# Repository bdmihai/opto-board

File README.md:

# opto-board

A small isolated interface board that lets a microcontroller set and read analog voltages and exchange digital ON/OFF signals with a separate high-voltage domain. Nothing connects the two sides except the optocouplers, so ground loops and interference stay out of the low-voltage electronics. The board is designed in KiCad and was built as a test fixture.

## Schematic

The board has two kinds of channels across the isolation barrier.

**Digital (4 × PC817).** These carry ON/OFF signals, such as an active-low fault input. On the HV side, a 4.7 kΩ pull-up to +15 V drives the LED with about 2.9 mA. On the LV side, the phototransistor pulls a 10 kΩ pull-up to 3.3 V low, and a 10 nF capacitor filters short spikes. That only needs a CTR of about 19 %, well under the 50 % the PC817 guarantees. In the MCU → HV direction, the MCU pin sources the LED current, so an unpowered MCU leaves the output in a safe state.

**Analog (2 × HCNR201).** These carry 0–3.3 V on the MCU side and 0–10 V on the HV side, in both directions: one channel sets a voltage and one measures it. Each HCNR201 has one LED and two matched photodiodes. An op-amp servo loop drives the LED so that the input photodiode current equals V_IN / R_IN. This cancels out LED drift from temperature, part spread and aging. On the other side, a transimpedance amplifier turns the output photodiode current back into a voltage:

V_OUT / V_IN = K3 · R_OUT / R_IN

K3 differs from part to part, so R_OUT includes a trimmer and each channel is calibrated once. The full-scale photodiode current of about 25 µA sits in the linear range of the HCNR201, where the datasheet specifies 0.05 % nonlinearity.

The LV side runs from 12 V through a fuse, a TVS diode and a buck converter that makes 3.3 V. The HV side is powered from the +15 V auxiliary output of the device being controlled. A 10 MΩ bleed (2 × 20 MΩ) connects HV_GND to GND so the HV ground cannot float to an arbitrary voltage.

## Board layout

| | |
|---|---|
| Size | 65 × 75 mm, 1.6 mm FR-4, 4 layers |
| Isolation slot | 55 × 5 mm, milled through the board |
| Copper-free gap | 9 mm between domains on every layer, including the inner planes |
| Narrowest point | PC817 package, 7.62 mm between the pad rows |
| Indicators | PWR, FAULT, OVT and EOCH LEDs on the LV side |

No copper from one domain runs under the other one on any layer. The slot forces surface creepage to go around it instead of straight across. This is a test board: the spacing is a design target, not a certified isolation rating.

## PCB production

[PCBWay](https://www.pcbway.com/) manufactured the PCBs as part of a sponsorship. 

The isolation slot was milled cleanly, there were no solder mask, copper or via defects, and the matte solder mask made hand soldering easy. The board worked on the first try and did the job!

## Results

In a loopback test (setpoint output wired to the measurement input, 2360 readings), the gain error was −0.13 % and 94 % of readings fell within one 8-bit step of the setpoint. Each channel behaves like a low-pass filter of about 1 kHz, and the full loopback settles in about 1.5 ms.

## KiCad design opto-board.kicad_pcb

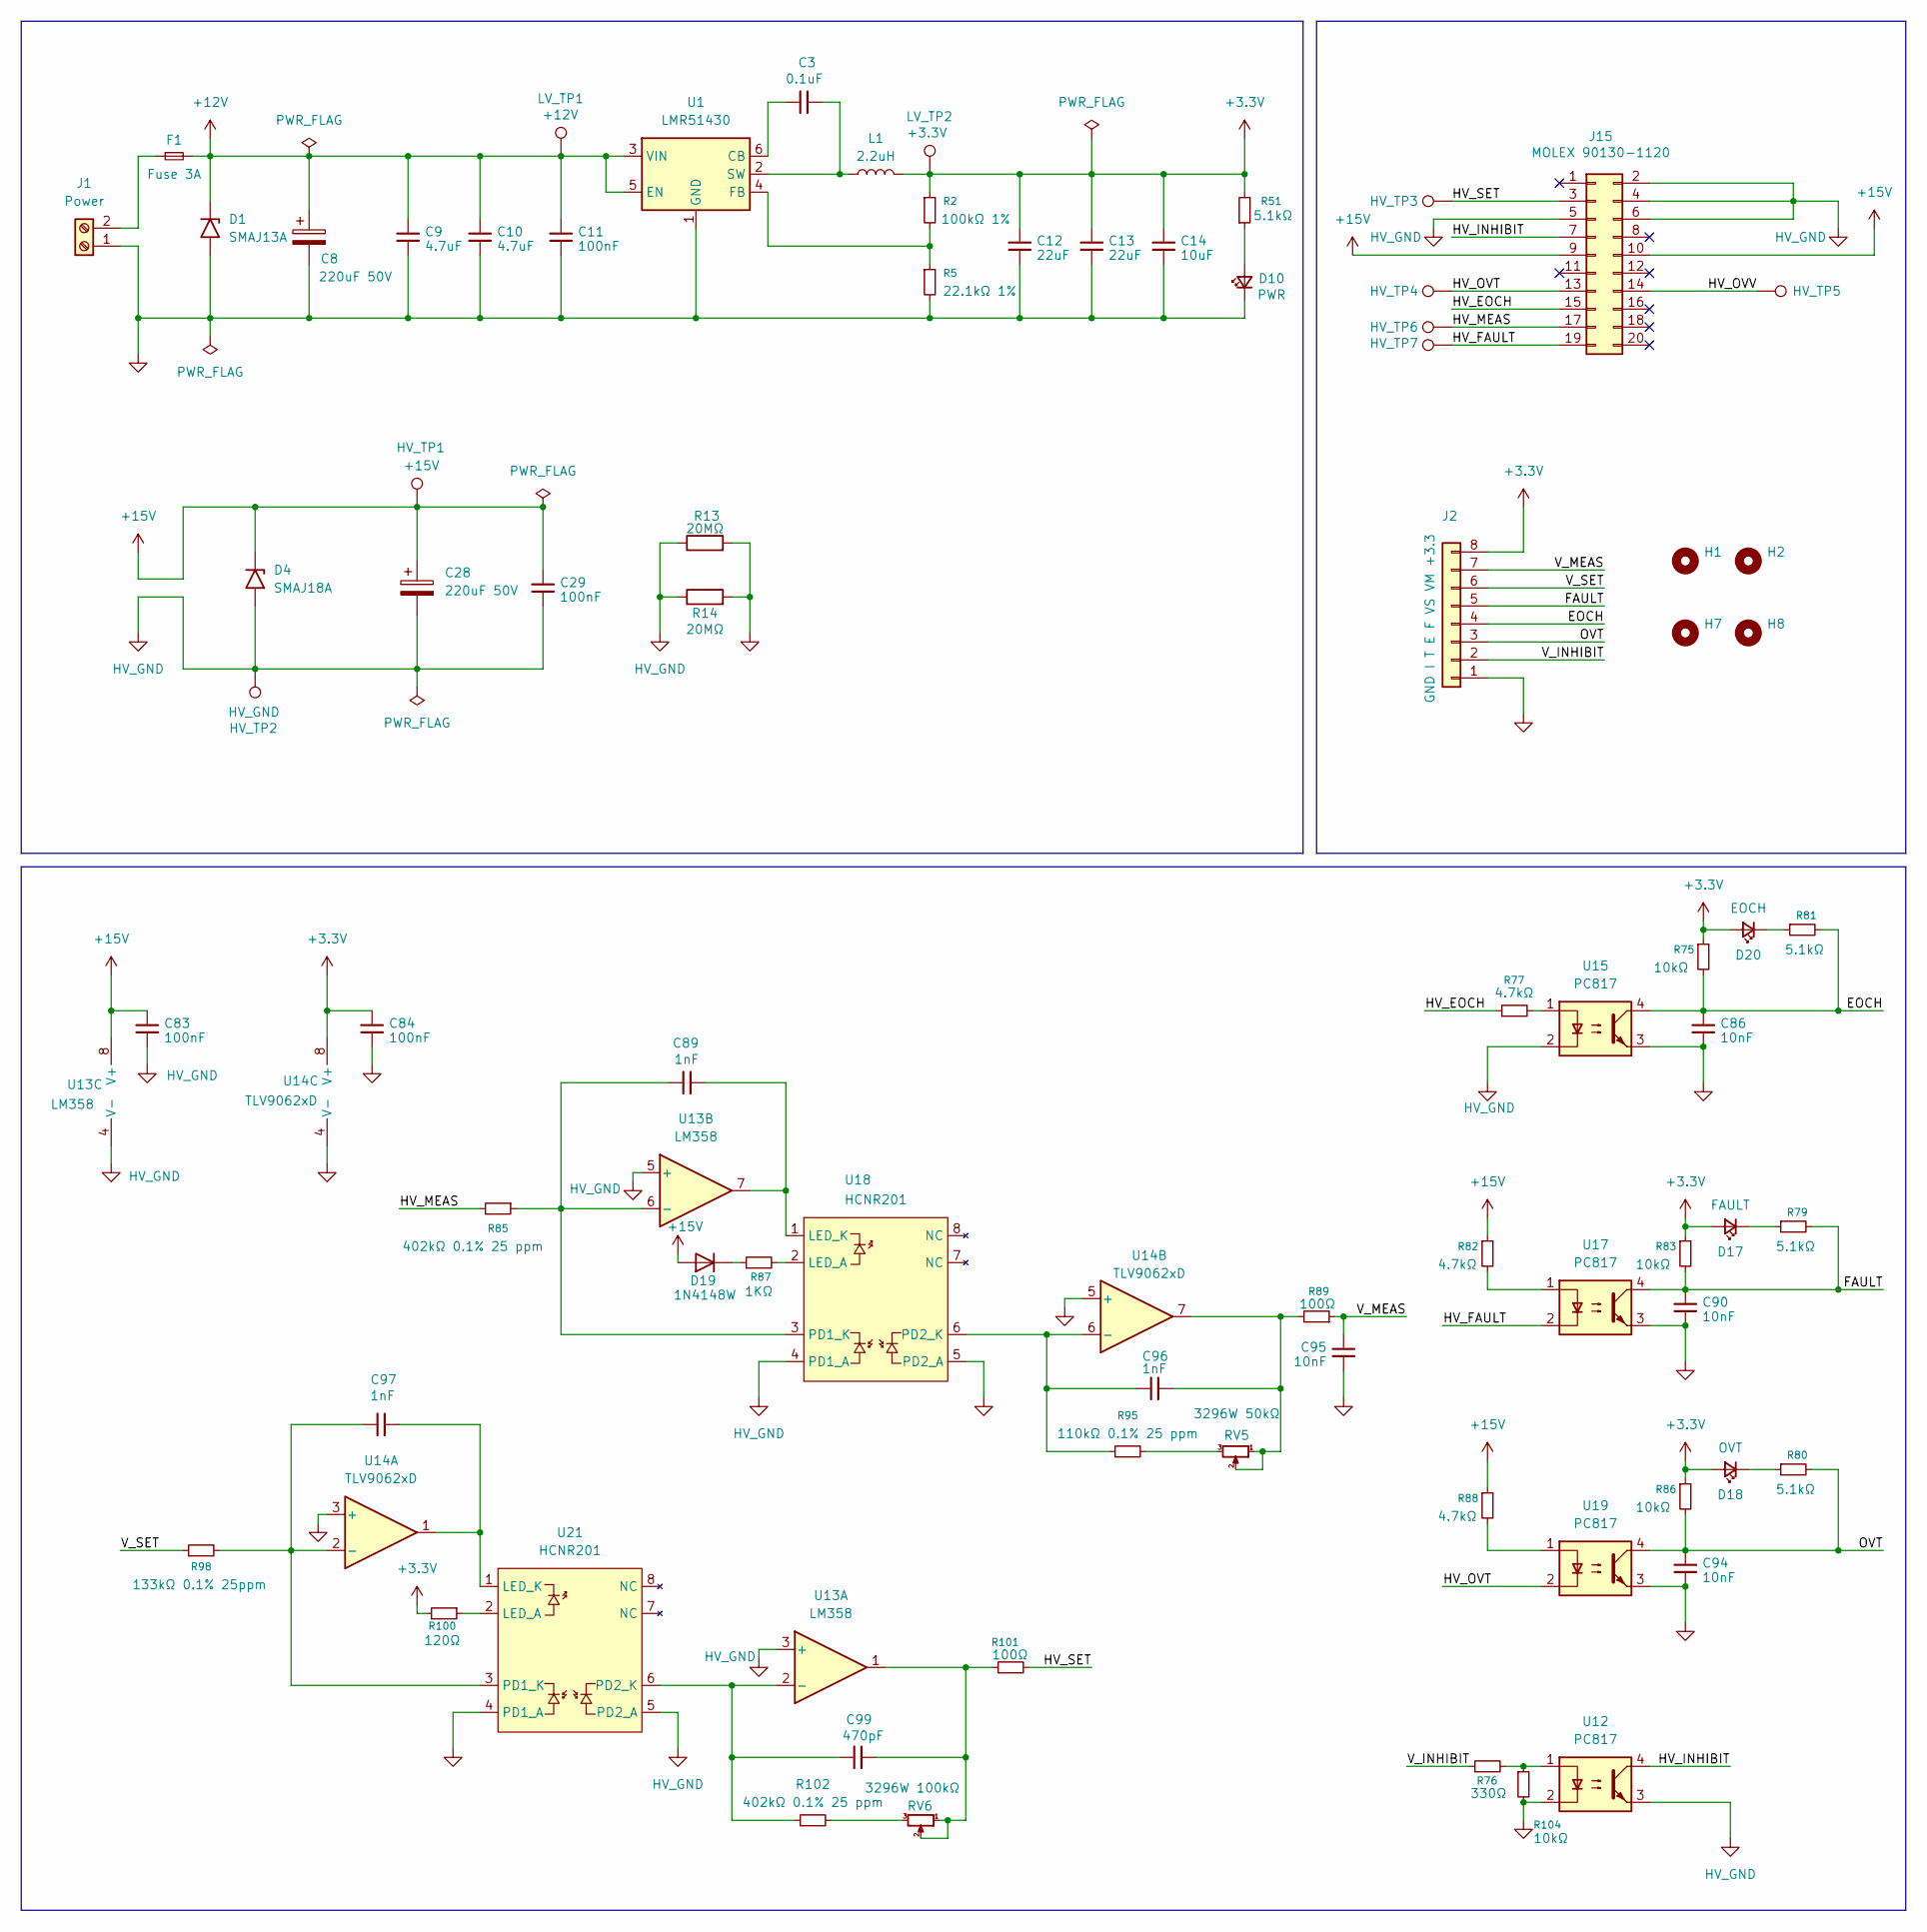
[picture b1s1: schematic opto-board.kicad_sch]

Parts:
C3: 0.1uF; C_0402_1005Metric
C8, C28: 220uF 50V; CP_Radial_D10.0mm_P5.00mm
C9, C10: 4.7uF; C_0805_2012Metric
C11, C29, C83, C84: 100nF; C_0402_1005Metric
C12, C13: 22uF; C_1210_3225Metric
C14: 10uF; C_0805_2012Metric
C86, C90, C94, C95: 10nF; C_0402_1005Metric
C89, C96, C97: 1nF; C_0402_1005Metric
C99: 470pF; C_0402_1005Metric
D1: SMAJ13A; D_SMA
D4: SMAJ18A; D_SMA
D10: PWR; LED_0805_2012Metric
D17: FAULT; LED_0805_2012Metric
D18: OVT; LED_0805_2012Metric
D19: 1N4148W; D_SOD-123
D20: EOCH; LED_0805_2012Metric
F1: Fuse 3A; Fuse_1206_3216Metric
H1, H2, H7, H8: MountingHole; MountingHole_3mm
HV_TP1: +15V; TestPoint_Pad_D1.0mm
HV_TP2: HV_GND; TestPoint_Pad_D1.0mm
HV_TP3: HV_SET; TestPoint_Pad_D1.0mm
HV_TP4: HV_OVT; TestPoint_Pad_D1.0mm
HV_TP5: HV_OVV; TestPoint_Pad_D1.0mm
HV_TP6: HV_MEAS; TestPoint_Pad_D1.0mm
HV_TP7: HV_FAULT; TestPoint_Pad_D1.0mm
J1: Power; TerminalBlock_Phoenix_MKDS-1,5-2-5.08_1x02_P5.08mm_Horizont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
J2: GND I T E F VS VM +3.3; PinHeader_1x08_P2.54mm_Horizontal
J15: MOLEX 90130-1120; IDC-Header_2x10_P2.54mm_Vertical
L1: 2.2uH; IND_SRP5030CA_BRN
LV_TP1: +12V; TestPoint_Pad_D1.0mm
LV_TP2: +3.3V; TestPoint_Pad_D1.0mm
R2: 100kΩ 1%; R_0402_1005Metric
R5: 22.1kΩ 1%; R_0402_1005Metric
R13, R14: 20MΩ; R_Axial_DIN0207_L6.3mm_D2.5mm_P15.24mm_Horizontal
R51, R79, R80, R81: 5.1kΩ; R_0402_1005Metric
R75, R83, R86, R104: 10kΩ; R_0402_1005Metric
R76: 330Ω; R_0402_1005Metric
R77, R82, R88: 4.7kΩ; R_0603_1608Metric
R85, R102: 402kΩ 0.1% 25 ppm; R_0603_1608Metric
R87: 1KΩ; R_1206_3216Metric
R89, R101: 100Ω; R_0402_1005Metric
R95: 110kΩ 0.1% 25 ppm; R_0603_1608Metric
R98: 133kΩ 0.1% 25ppm; R_0603_1608Metric
R100: 120Ω; R_0603_1608Metric
RV5: 3296W 50kΩ; Potentiometer_Bourns_3296W_Vertical
RV6: 3296W 100kΩ; Potentiometer_Bourns_3296W_Vertical
U1: LMR51430; SOT-23-6
U12, U15, U17, U19: PC817; PC817_SMDIP-4_W7.62mm
U13: LM358; SOIC-8_3.9x4.9mm_P1.27mm
U14: TLV9062xD; SOIC-8_3.9x4.9mm_P1.27mm
U18, U21: HCNR201; HCNR201_SMDIP-8_W11.48mm

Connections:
+3.3V: C12.1, C13.1, C14.1, C84.1, D17.2 (A), D18.2 (A), D20.2 (A), J2.8, L1.2, LV_TP2.1 (1_1), R2.1, R51.2, R75.1, R83.1, R86.1, R100.2, U14.8 (V+)
+12V: C8.1, C9.1, C10.1, C11.1, D1.1 (A1), F1.2, LV_TP1.1 (1_1), U1.3 (VIN), U1.5 (EN)
+15V: C28.1, C29.1, C83.1, D4.1 (A1), D19.2 (A), HV_TP1.1 (1_1), J15.9, J15.10, R82.1, R88.1, U13.8 (V+)
/EOCH: C86.1, J2.4, R75.2, R81.2, U15.4
/FAULT: C90.1, J2.5, R79.2, R83.2, U17.4
/HV_EOCH: J15.15, R77.1
/HV_FAULT: HV_TP7.1, J15.19, U17.2; also elsewhere on the board
/HV_INHIBIT: J15.7, U12.4
/HV_MEAS: HV_TP6.1, J15.17, R85.2; also elsewhere on the board
/HV_OVT: HV_TP4.1, J15.13, U19.2; also elsewhere on the board
/HV_OVV: HV_TP5.1 (1_1), J15.14
/HV_SET: HV_TP3.1, J15.3, R101.2; also elsewhere on the board
/OVT: C94.1, J2.3, R80.2, R86.2, U19.4
/V_INHIBIT: J2.2, R76.1
/V_MEAS: C95.1, J2.7, R89.1
/V_SET: J2.6, R98.1
GND: C8.2, C9.2, C10.2, C11.2, C12.2, C13.2, C14.2, C84.2, C86.2, C90.2, C94.2, C95.2, D1.2 (A2), D10.1 (K), J1.1, J2.1, R5.2, R13.2, R14.2, R104.2, U1.1 (GND), U12.2, U14.3 (+), U14.4 (V-), U14.5 (+), U15.3, U17.3, U18.5 (PD2_A), U19.3, U21.4 (PD1_A)
HV_GND: C28.2, C29.2, C83.2, D4.2 (A2), HV_TP2.1 (1_1), J15.2, J15.4, J15.5, J15.6, R13.1, R14.1, U12.3, U13.3 (+), U13.4 (V-), U13.5 (+), U15.2, U18.4 (PD1_A), U21.5 (PD2_A)
unnamed: C96.2, R89.2, RV5.1, RV5.2, U14.7
unnamed: C99.1, R101.1, RV6.1, RV6.2, U13.1
unnamed: D10.2 (A), R51.1
unnamed: D17.1 (K), R79.1
unnamed: D18.1 (K), R80.1
unnamed: D19.1 (K), R87.1
unnamed: D20.1 (K), R81.1
unnamed: F1.1, J1.2
unnamed: R77.2, U15.1
unnamed: R82.2, U17.1
unnamed: R88.2, U19.1
unnamed: R95.2, RV5.3
unnamed: R102.2, RV6.3
unnamed: R76.2, R104.1, U12.1
unnamed: C3.1, U1.6 (CB)
unnamed: R2.2, R5.1, U1.4 (FB)
unnamed: C3.2, L1.1, U1.2 (SW)
unnamed: C99.2, R102.1, U13.2 (-), U21.6 (PD2_K)
unnamed: C89.1, R85.1, U13.6 (-), U18.3 (PD1_K)
unnamed: C97.1, R98.2, U14.2 (-), U21.3 (PD1_K)
unnamed: C96.1, R95.1, U14.6 (-), U18.6 (PD2_K)
unnamed: R87.2, U18.2 (LED_A)
unnamed: C89.2, U13.7, U18.1 (LED_K)
unnamed: R100.1, U21.2 (LED_A)
unnamed: C97.2, U14.1, U21.1 (LED_K)

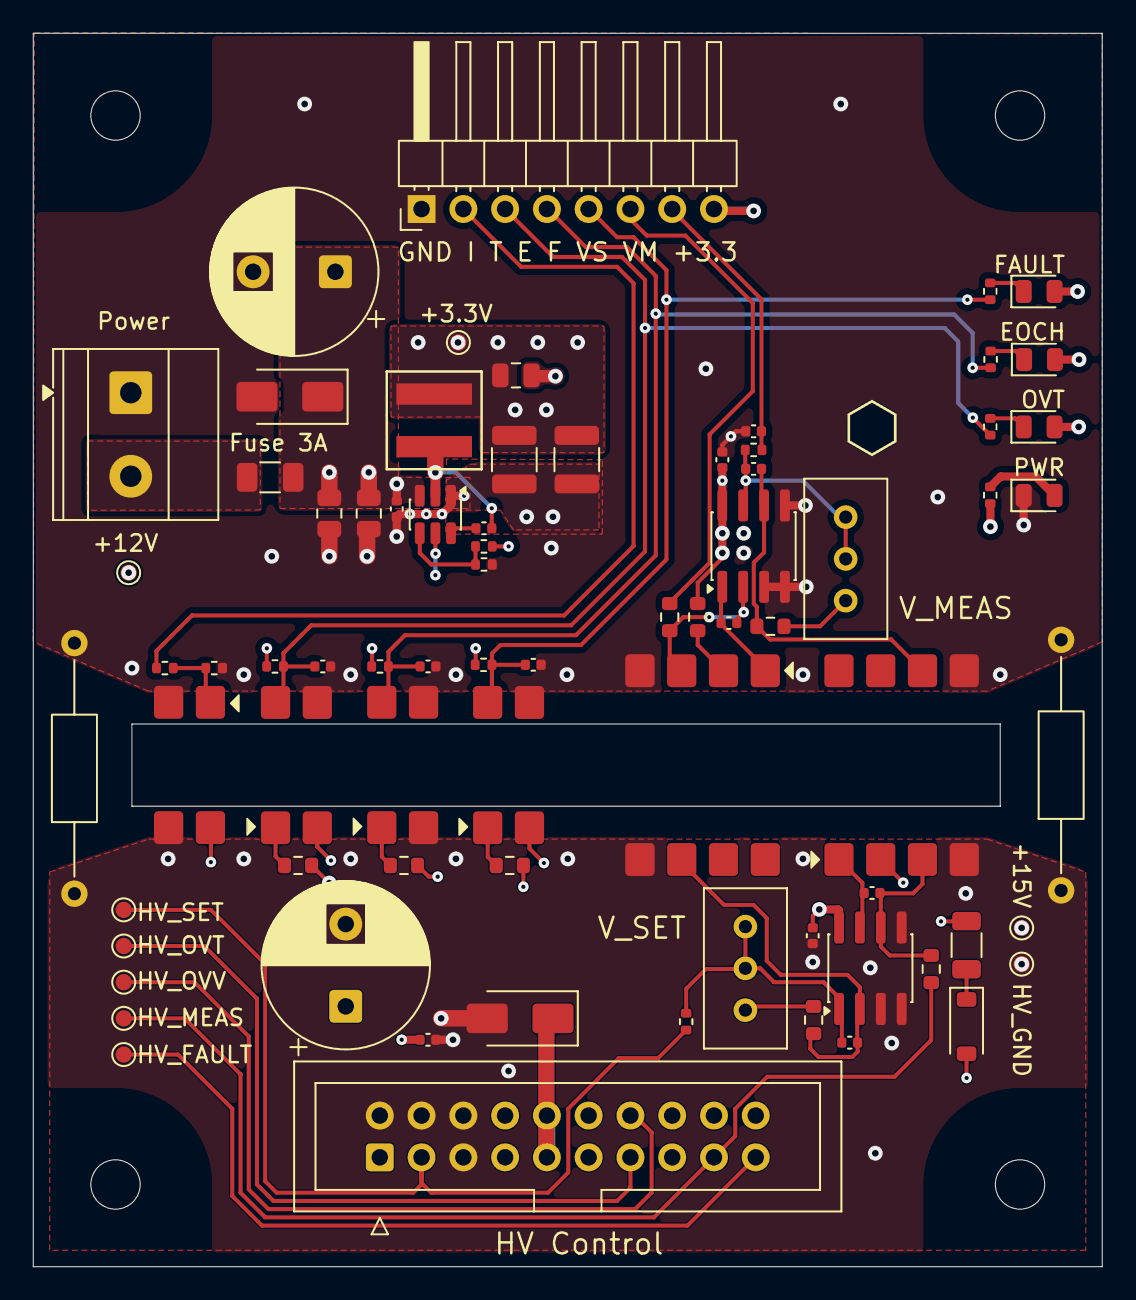
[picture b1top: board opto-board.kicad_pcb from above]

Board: 4 copper layers, 65.0 x 75.0 mm, 80 parts (0 on the bottom side), 43 nets.

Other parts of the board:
HV_PSU_TP3: HV_SET; TestPoint_Pad_D1.0mm
HV_PSU_TP4: HV_OVT; TestPoint_Pad_D1.0mm
HV_PSU_TP6: HV_MEAS; TestPoint_Pad_D1.0mm
HV_PSU_TP7: HV_FAULT; TestPoint_Pad_D1.0mm

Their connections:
/HV_FAULT: HV_PSU_TP7.1 (1_1); also elsewhere on the board
/HV_MEAS: HV_PSU_TP6.1 (1_1); also elsewhere on the board
/HV_OVT: HV_PSU_TP4.1 (1_1); also elsewhere on the board
/HV_SET: HV_PSU_TP3.1 (1_1); also elsewhere on the board
